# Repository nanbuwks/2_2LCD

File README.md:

It is design of 3.2in LCD module  
http://www.lcdwiki.com/3.2inch_SPI_Module_ILI9341_SKU:MSP321

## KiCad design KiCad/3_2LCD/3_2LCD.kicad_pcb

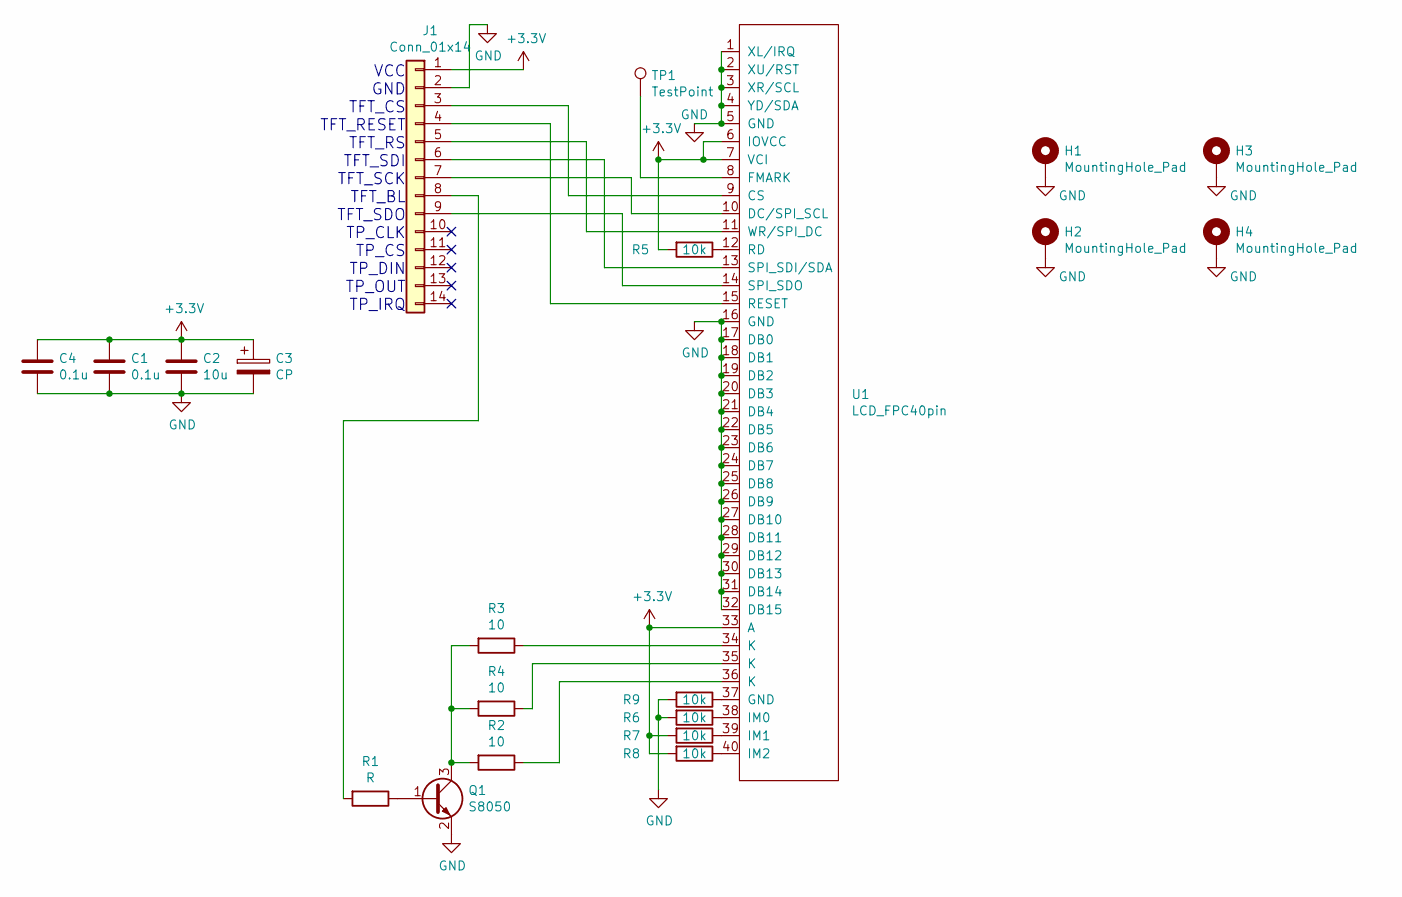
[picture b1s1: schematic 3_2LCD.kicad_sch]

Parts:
C1, C4: 0.1u; C_0603_1608Metric
C2: 10u; C_0402_1005Metric
C3: CP; CP_Radial_D5.0mm_P2.50mm
H1, H2, H3, H4: MountingHole_Pad; MountingHole_2.7mm_M2.5_Pad_TopBottom
J1: Conn_01x14; PinHeader_1x14_P2.54mm_Vertical
Q1: S8050; SOT-23
R1: R; R_0603_1608Metric
R2, R3, R4: 10; R_0603_1608Metric
R5, R6, R7, R8, R9: 10k; R_0603_1608Metric
TP1: TestPoint; TestPoint_Keystone_5000-5004_Miniature
U1: LCD_FPC40pin; Hirose_40P0.50mm_Horizontal_Reverse

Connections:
+3V3: C1.1, C2.1, C3.1, C4.1, J1.1, R5.2, R7.2, R8.2, U1.6 (IOVCC), U1.7 (VCI), U1.33 (A)
GND: C1.2, C2.2, C3.2, C4.2, H1.1, H2.1, H3.1, H4.1, J1.2, Q1.2 (E), R6.2, R9.2, U1.1 (XL/IRQ), U1.2 (XU/RST), U1.3 (XR/SCL), U1.4 (YD/SDA), U1.5 (GND), U1.16 (GND), U1.17 (DB0), U1.18 (DB1), U1.19 (DB2), U1.20 (DB3), U1.21 (DB4), U1.22 (DB5), U1.23 (DB6), U1.24 (DB7), U1.25 (DB8), U1.26 (DB9), U1.27 (DB10), U1.28 (DB11), U1.29 (DB12), U1.30 (DB13), U1.31 (DB14), U1.32 (DB15)
unnamed: J1.3, U1.9 (CS)
unnamed: J1.4, U1.15 (RESET)
unnamed: J1.5, U1.11 (WR/SPI_DC)
unnamed: J1.6, U1.13 (SPI_SDI/SDA)
unnamed: J1.7, U1.10 (DC/SPI_SCL)
unnamed: J1.8, R1.2
unnamed: J1.9, U1.14 (SPI_SDO)
unnamed: Q1.1 (B), R1.1
unnamed: Q1.3 (C), R2.2, R3.2, R4.2
unnamed: R2.1, U1.36 (K)
unnamed: R3.1, U1.34 (K)
unnamed: R4.1, U1.35 (K)
unnamed: R9.1, U1.37 (GND)
unnamed: TP1.1, U1.8 (FMARK)
unnamed: R6.1, U1.38 (IM0)
unnamed: R7.1, U1.39 (IM1)
unnamed: R8.1, U1.40 (IM2)
unnamed: R5.1, U1.12 (RD)

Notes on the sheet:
VCC GND TFT_CS TFT_RESET TFT_RS TFT_SDI TFT_SCK TFT_BL TFT_SDO TP_CLK TP_CS TP_DIN TP_OUT TP_IRQ

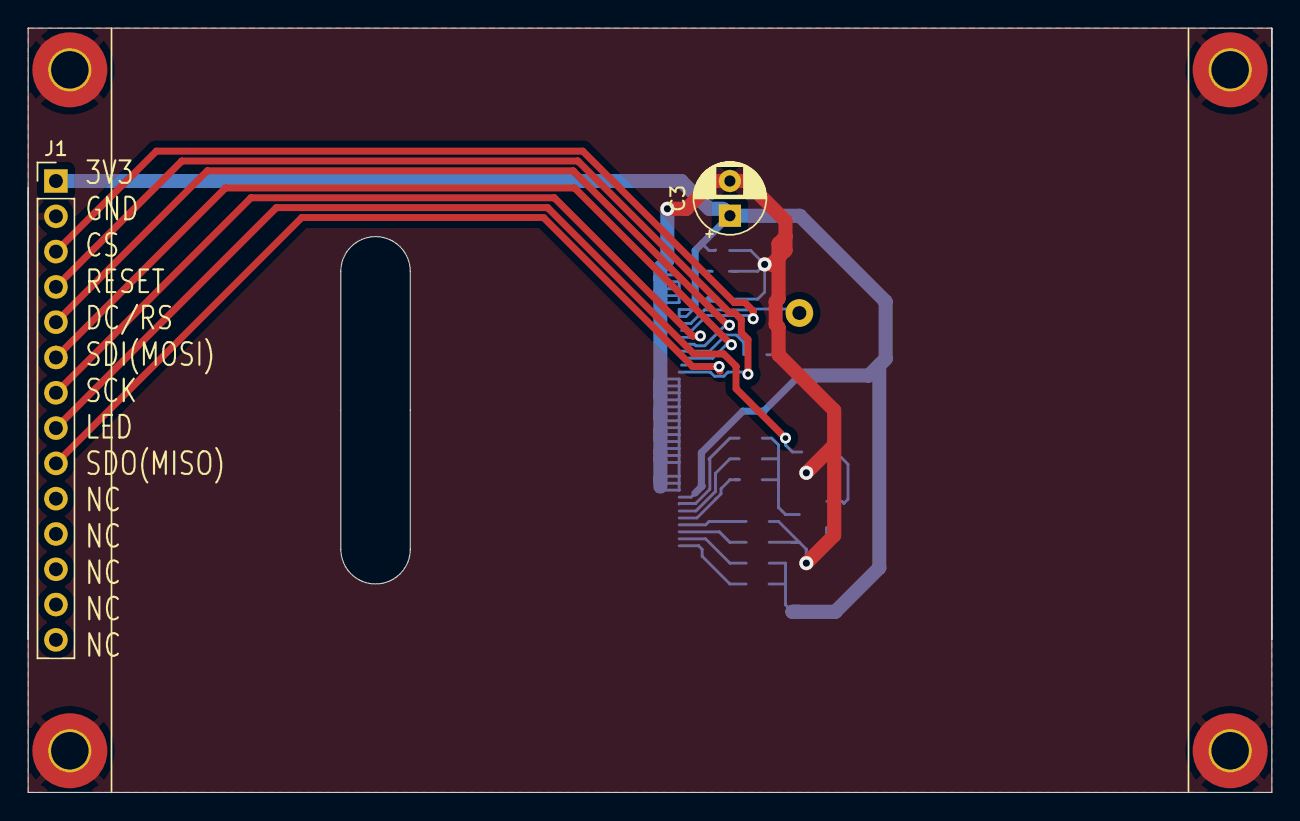
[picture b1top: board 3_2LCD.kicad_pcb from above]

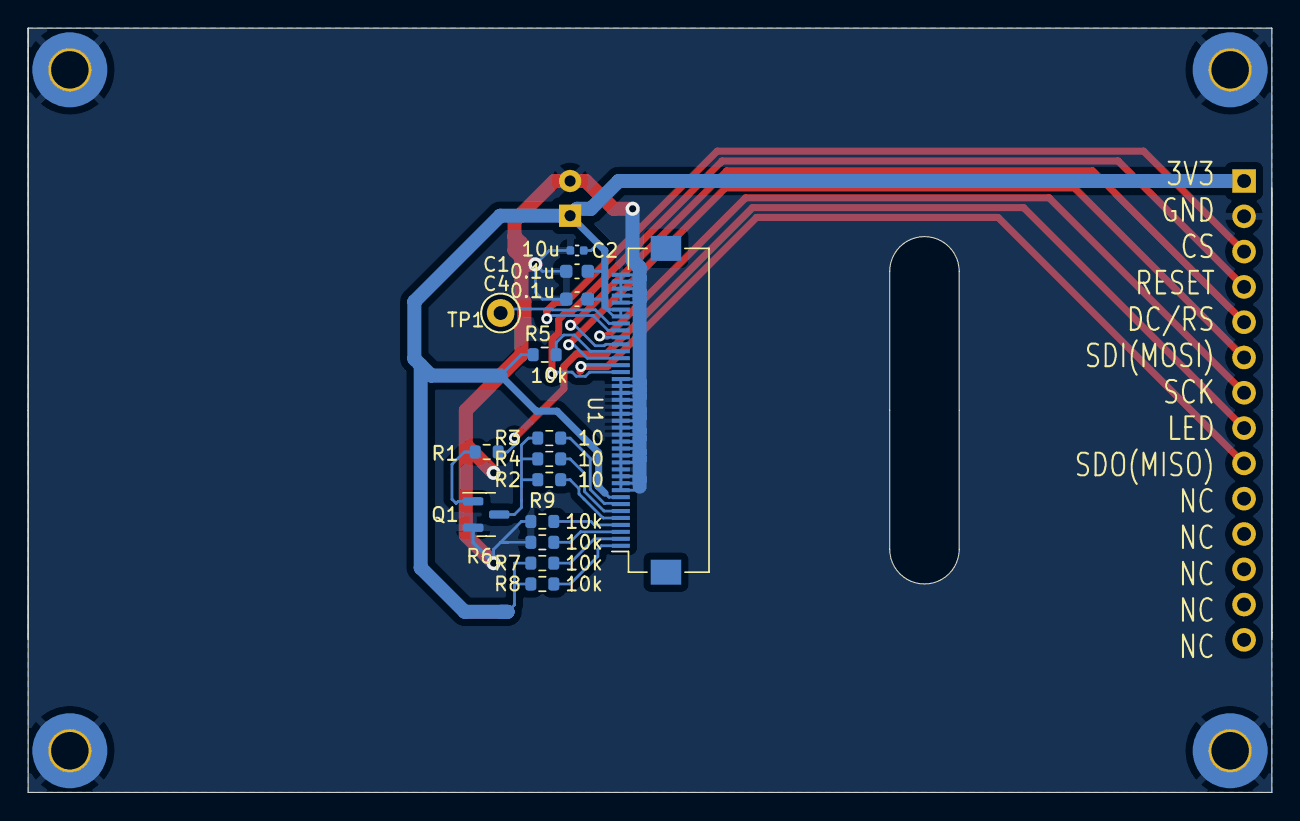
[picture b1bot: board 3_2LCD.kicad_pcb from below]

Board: 2 copper layers, 89.5 x 55.0 mm, 21 parts (15 on the bottom side), 20 nets.

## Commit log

2023-09-11 change to KiCad7
